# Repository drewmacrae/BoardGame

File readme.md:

# Board Game

I heard an idea that was too good not to act on the other day, so here is a couple of board games that use RGB LEDs in lieue of colorful marbles. The goal is to enable correspondence play of some gimes (and the original idea was centered on a game called "Chinese Checkers" in the US where it was invented by modifying a German game that could be played on a square board.

## Project Structure

I have a license of Solidworks 2014 on my machine so I used that for the 3D CAD, but I don't think it's good.
I wanted to play with a newer ECAD solution than I have a license to so now I'm learning to use KICAD(pronounced however you want maybe)... LMK if I do weird things in it. I probably just don't know better.
Software is not yet included or written.
The board and BOM are all for Through Hole parts. They're more expensive, but this enables easier debugging and better assembly processes early on. It also means it could be shared as a hobby kit, rather than a finished piece.

# Considerations

There's a number of considerations that drove the design of this. 

## Hobby Friendliness

Because we're developing this as a hobby and don't want to place the goalposts too far ahead, we're going to try to make hobby friendly decisions wherever we can. That's why we're writing this documentation, why we're using Through Hole parts, and why we're using SPI to control each of the peripheral parts. That's why there's a single plastic part design and the PCB is used for the majority of the structure. The 5V power supply lets us use USB adapters.

## Accessibility

We want to enable play with people who might need help setting this up and for it to function for people who might struggle with WIFI and touchscreens.

## Price

There's a lot of spaces on a Chinese Checkers board, and a lot of players. Correspondence play could get very expensive very fast if we're not careful

# Goals

Up front we want to recognize a number of product goals. These may conflict, but they're valuable enough to be worth seeking in their own right.

## 0 cost to participate in games

Let's make an online frontend so someone can play games without the hardware, and maybe so that more than one player can use the same board.

## One version in PTH

If these things are all surface mount (SMT) rather than through hole (PTH) assembly will be another thing that someone will need to plan for and manage. I'd rather start with a PTH version and be able to send kits to interested parties easily especially starting off. Soldering is fun and a kit is a nice way to organize simple projects like this for sharing.

## One version without WIFI

We want itto work for users without WIFI access. This might be hard/annoying/expensive, but having an SPI driver that can control this board and call in moves through an alternate network is interesting.

## One version with clicky buttons

# Design

## Server

## Web Client

## Current control

Cheap display LEDs have variable voltage drops which leads to variation in brightness if LEDs are powered with similar voltages. I prefer current control when available and this is often available in row drivers.

## LED matrix vs individual control

World Semi and a few other companies make LEDs that can be well controlled in very long strings. These require each string be driven in a timing critical manner for each frame update. I prefer to use drivers that let me leverage serial peripherals, even if the update rate is accelerated (the peripheral lets us do so in a way that's more convenient in the hardware.)

# Authors

* **Andrew Macrae** - *Initial work* 
* **Ryan Menefee** - *Concept and review*

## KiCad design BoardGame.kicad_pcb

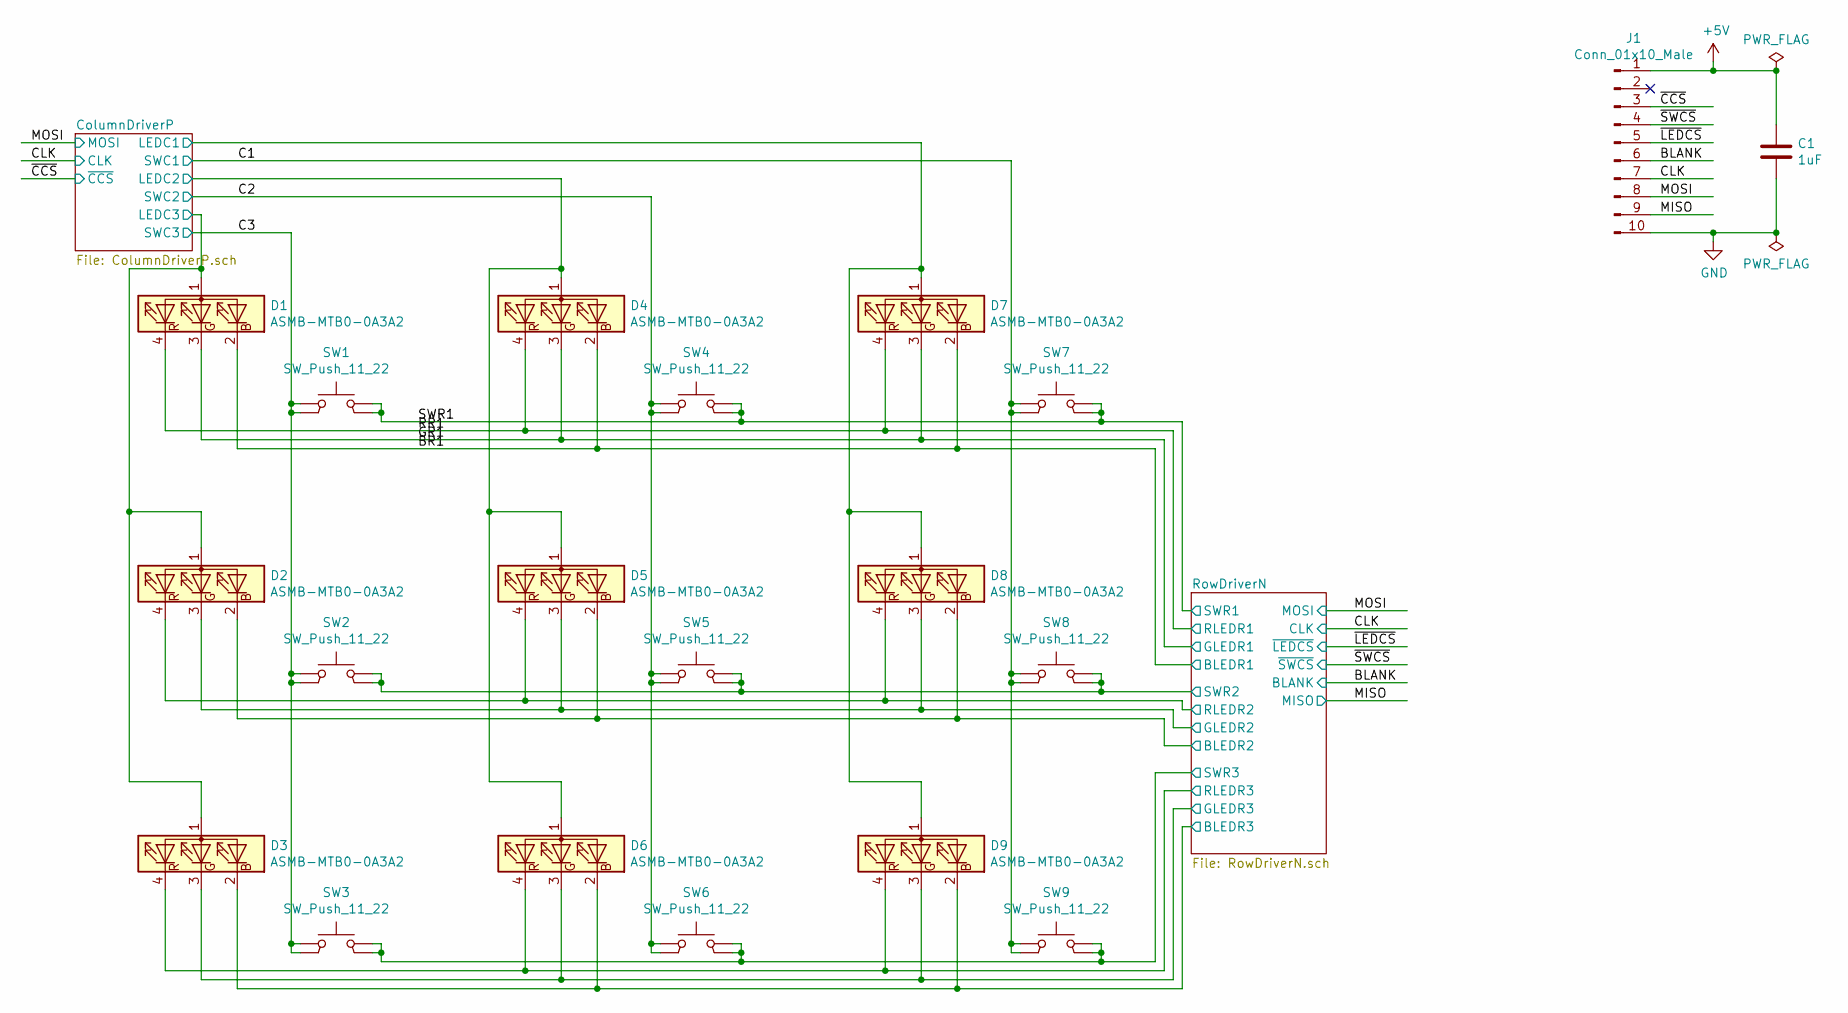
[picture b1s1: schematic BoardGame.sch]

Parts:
C1: 1uF; CP_Radial_D5.0mm_P2.50mm
D1, D2, D3, D4, D5, D6, D7, D8, D9: ASMB-MTB0-0A3A2; LED_D5.0mm-4_RGB
J1: Conn_01x10_Male; PinHeader_1x10_P2.54mm_Horizontal
SW1, SW2, SW3, SW4, SW5, SW6, SW7, SW8, SW9: SW_Push_11_22; SW_PUSH_6mm

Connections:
+5V: C1.1, J1.1; also elsewhere on the board
/BLANK: J1.6; also elsewhere on the board
/BR1: D1.2 (BK), D4.2 (BK), D7.2 (BK); also elsewhere on the board
/C1: D7.1 (A), D8.1 (A), D9.1 (A), SW7.1, SW8.1, SW9.1; also elsewhere on the board
/C2: D4.1 (A), D5.1 (A), D6.1 (A), SW4.1, SW5.1, SW6.1; also elsewhere on the board
/C3: D1.1 (A), D2.1 (A), D3.1 (A), SW1.1, SW2.1, SW3.1; also elsewhere on the board
/CLK: J1.7; also elsewhere on the board
/GR1: D1.3 (GK), D4.3 (GK), D7.3 (GK); also elsewhere on the board
/MISO: J1.9; also elsewhere on the board
/MOSI: J1.8; also elsewhere on the board
/RR1: D1.4 (RK), D4.4 (RK), D7.4 (RK); also elsewhere on the board
/RowDriverN/BLEDR2: D2.2 (BK), D5.2 (BK), D8.2 (BK); also elsewhere on the board
/RowDriverN/BLEDR3: D3.2 (BK), D6.2 (BK), D9.2 (BK); also elsewhere on the board
/RowDriverN/GLEDR2: D2.3 (GK), D5.3 (GK), D8.3 (GK); also elsewhere on the board
/RowDriverN/GLEDR3: D3.3 (GK), D6.3 (GK), D9.3 (GK); also elsewhere on the board
/RowDriverN/RLEDR2: D2.4 (RK), D5.4 (RK), D8.4 (RK); also elsewhere on the board
/RowDriverN/RLEDR3: D3.4 (RK), D6.4 (RK), D9.4 (RK); also elsewhere on the board
/RowDriverN/SWR2: SW2.2, SW5.2, SW8.2; also elsewhere on the board
/RowDriverN/SWR3: SW3.2, SW6.2, SW9.2; also elsewhere on the board
/SWR1: SW1.2, SW4.2, SW7.2; also elsewhere on the board
/~CCS: J1.3; also elsewhere on the board
/~LEDCS: J1.5; also elsewhere on the board
/~SWCS: J1.4; also elsewhere on the board
GND: C1.2, J1.10; also elsewhere on the board

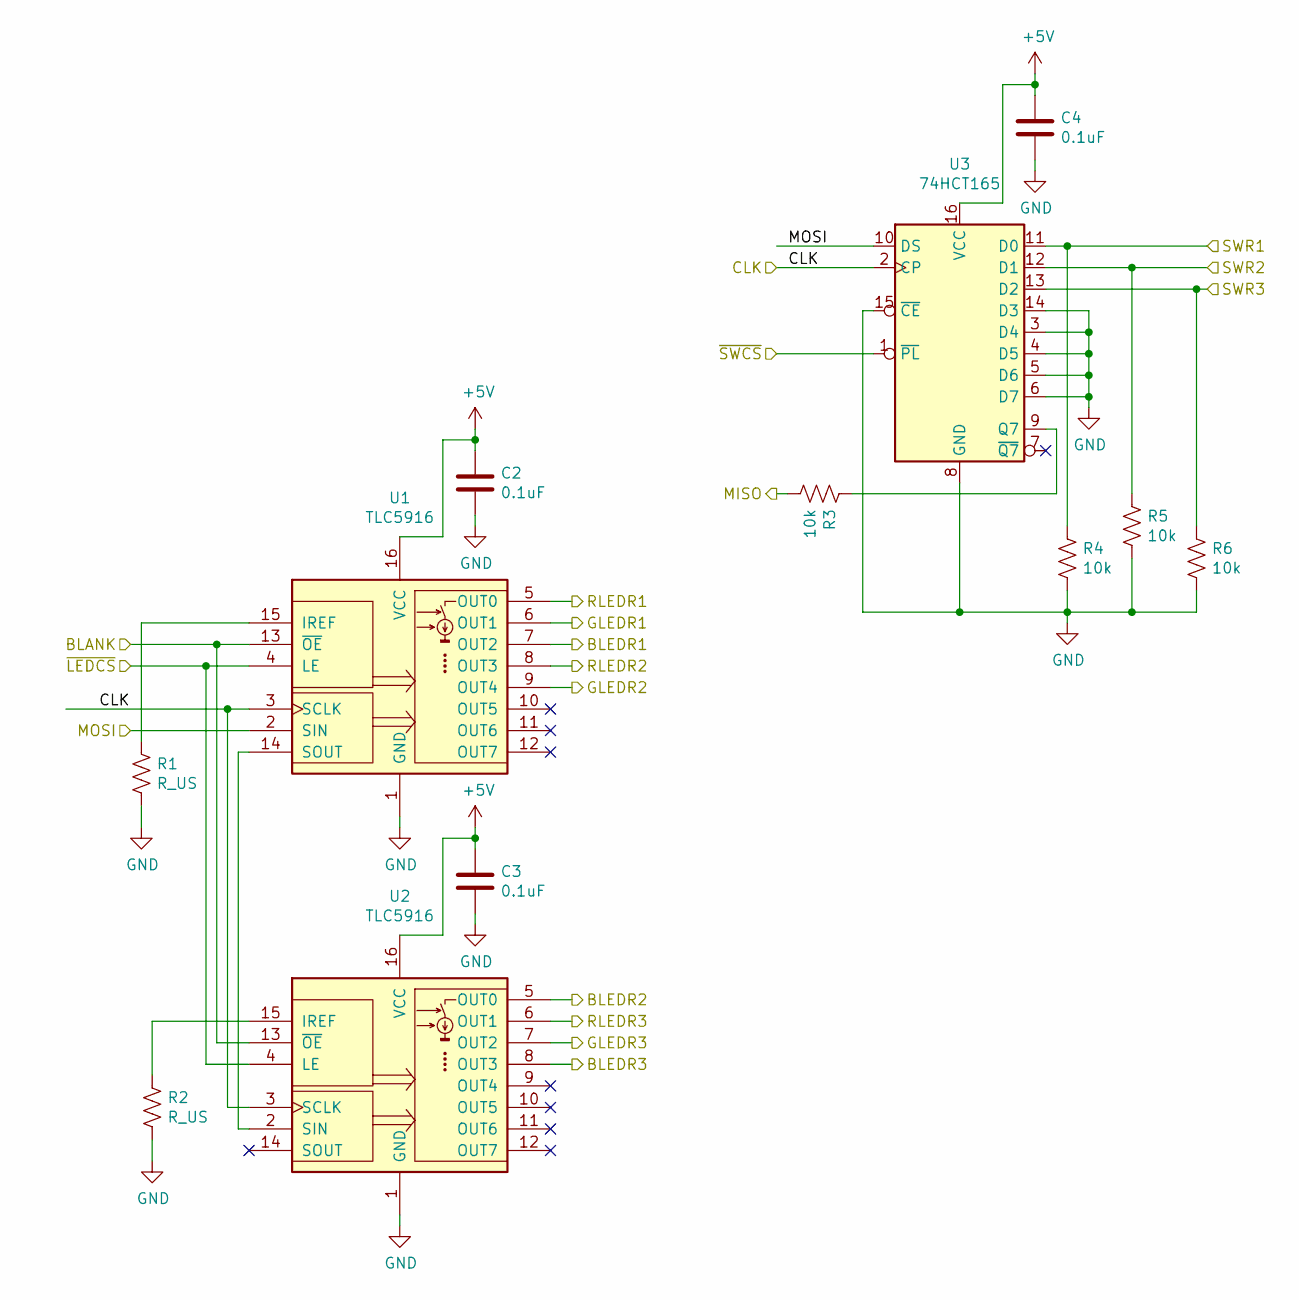
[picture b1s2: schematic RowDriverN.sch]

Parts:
C2, C3, C4: 0.1uF; C_Rect_L4.6mm_W3.0mm_P2.50mm_MKS02_FKP02
R1, R2: R_US; R_Axial_DIN0207_L6.3mm_D2.5mm_P7.62mm_Horizontal
R3, R4, R5, R6: 10k; R_Axial_DIN0207_L6.3mm_D2.5mm_P7.62mm_Horizontal
U1, U2: TLC5916; DIP-16_W7.62mm
U3: 74HCT165; DIP-16_W7.62mm

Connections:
+5V: C2.1, C3.1, C4.1, U1.16 (VCC), U2.16 (VCC), U3.16 (VCC); also elsewhere on the board
/BLANK: U1.13 (~OE), U2.13 (~OE); also elsewhere on the board
/BR1: U1.7 (OUT2); also elsewhere on the board
/CLK: U1.3 (SCLK), U2.3 (SCLK), U3.2 (CP); also elsewhere on the board
/GR1: U1.6 (OUT1); also elsewhere on the board
/MISO: R3.2; also elsewhere on the board
/MOSI: U1.2 (SIN), U3.10 (DS); also elsewhere on the board
/RR1: U1.5 (OUT0); also elsewhere on the board
/RowDriverN/BLEDR2: U2.5 (OUT0); also elsewhere on the board
/RowDriverN/BLEDR3: U2.8 (OUT3); also elsewhere on the board
/RowDriverN/GLEDR2: U1.9 (OUT4); also elsewhere on the board
/RowDriverN/GLEDR3: U2.7 (OUT2); also elsewhere on the board
/RowDriverN/RLEDR2: U1.8 (OUT3); also elsewhere on the board
/RowDriverN/RLEDR3: U2.6 (OUT1); also elsewhere on the board
/RowDriverN/SWR2: R5.1, U3.12 (D1); also elsewhere on the board
/RowDriverN/SWR3: R6.1, U3.13 (D2); also elsewhere on the board
/SWR1: R4.1, U3.11 (D0); also elsewhere on the board
/~LEDCS: U1.4 (LE), U2.4 (LE); also elsewhere on the board
/~SWCS: U3.1 (~PL); also elsewhere on the board
GND: C2.2, C3.2, C4.2, R1.2, R2.2, R4.2, R5.2, R6.2, U1.1 (GND), U2.1 (GND), U3.3 (D4), U3.4 (D5), U3.5 (D6), U3.6 (D7), U3.8 (GND), U3.14 (D3), U3.15 (~CE); also elsewhere on the board
unnamed: R1.1, U1.15 (IREF)
unnamed: R2.1, U2.15 (IREF)
unnamed: R3.1, U3.9 (Q7)
unnamed: U1.14 (SOUT), U2.2 (SIN)

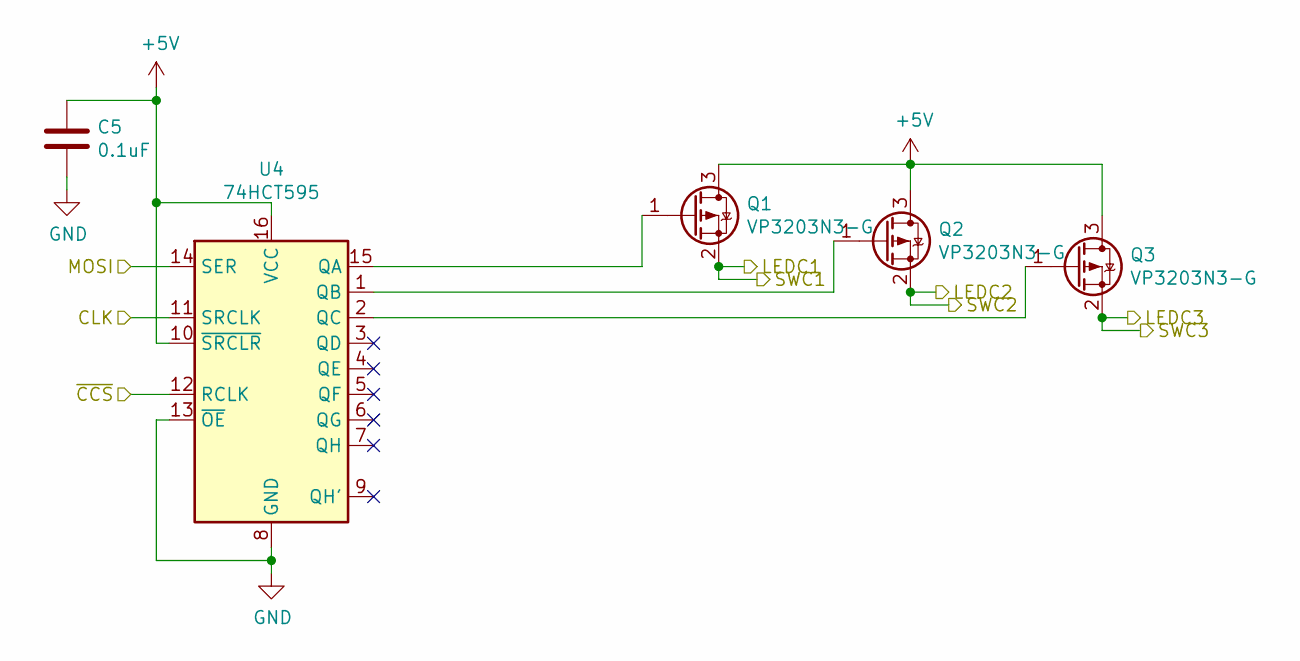
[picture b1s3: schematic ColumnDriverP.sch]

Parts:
C5: 0.1uF; C_Rect_L4.6mm_W3.0mm_P2.50mm_MKS02_FKP02
Q1, Q2, Q3: VP3203N3-G; TO-92
U4: 74HCT595; DIP-16_W7.62mm

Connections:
+5V: C5.1, Q1.3 (D), Q2.3 (D), Q3.3 (D), U4.10 (~SRCLR), U4.16 (VCC); also elsewhere on the board
/C1: Q1.2 (S); also elsewhere on the board
/C2: Q2.2 (S); also elsewhere on the board
/C3: Q3.2 (S); also elsewhere on the board
/CLK: U4.11 (SRCLK); also elsewhere on the board
/MOSI: U4.14 (SER); also elsewhere on the board
/~CCS: U4.12 (RCLK); also elsewhere on the board
GND: C5.2, U4.8 (GND), U4.13 (~OE); also elsewhere on the board
unnamed: Q1.1 (G), U4.15 (QA)
unnamed: Q2.1 (G), U4.1 (QB)
unnamed: Q3.1 (G), U4.2 (QC)

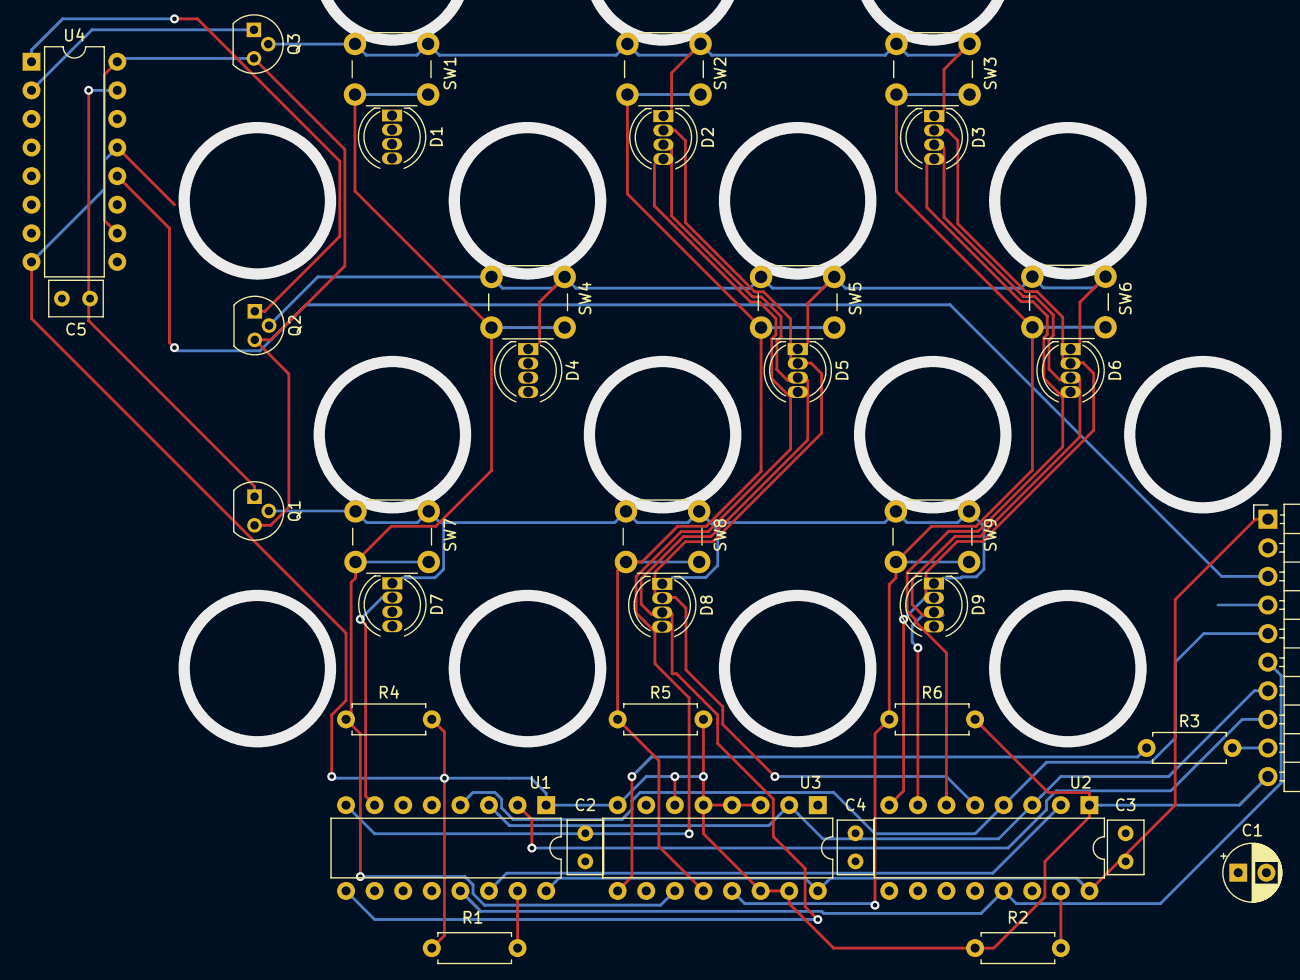
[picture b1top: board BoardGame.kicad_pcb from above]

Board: 2 copper layers, 37 parts (0 on the bottom side), 31 nets.

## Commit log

2019-12-01 First KiCad project in Github for me so let me know if there's anything
2020-01-04 Create HV-5RGBXX 5mm Full-Color Series.pdf
    added LED datasheet
2020-01-04 Added 3d cad for buttons
    3d cad for buttons including a step file showing 2, and the solidworks files from solidworks 2014
2020-01-06 Update readme.md
    still working, but taking a break so here's another commit
2020-01-11 Added caps to PCB
    I added cap footprints to the PCB
2020-01-12 Update BoardGame.kicad_pcb
    placements
2020-01-12 Update RowDriverN.sch
    Cleaned up row driver parts to point to correct datasheet.
    changed resistors to 1k for switches and level shifts and rext where they program about 20ma of LED current.
